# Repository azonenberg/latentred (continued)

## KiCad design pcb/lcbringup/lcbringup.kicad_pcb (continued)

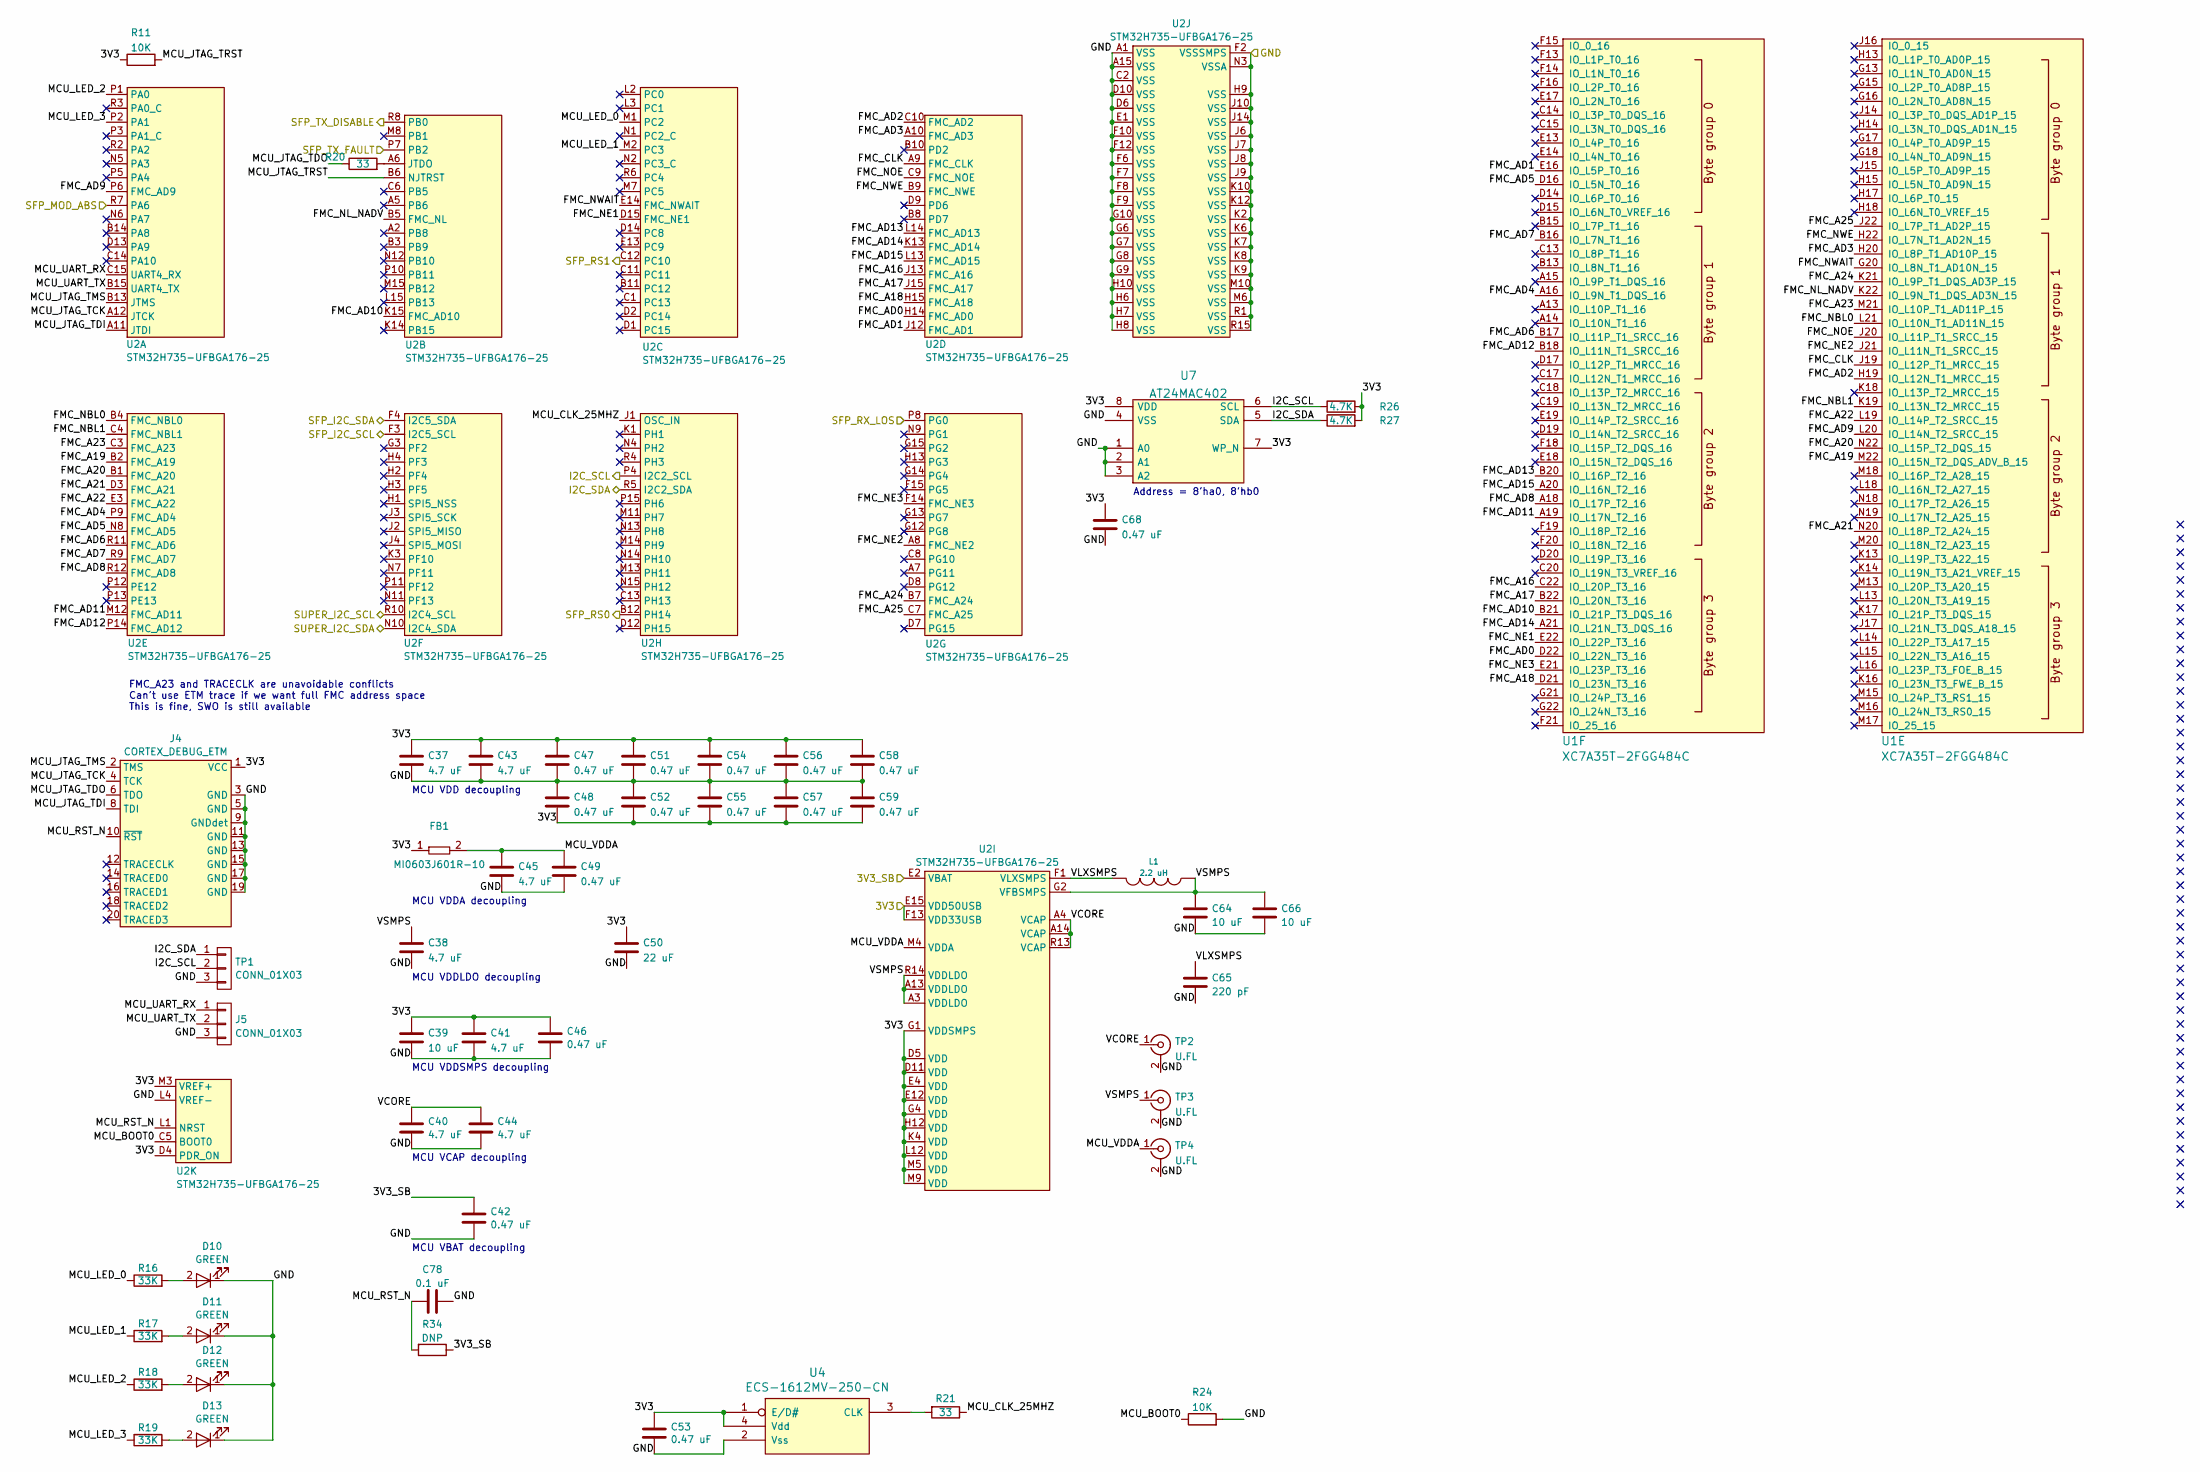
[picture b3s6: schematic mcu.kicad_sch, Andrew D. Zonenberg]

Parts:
C37, C38, C40, C41, C43, C44, C45: 4.7 uF; EIA_0603_CAP_NOSILK
C39, C64, C66: 10 uF; EIA_0805_CAP_NOSILK
C42, C46, C47, C48, C49, C51, C52, C53, C54, C55, C56, C57, C58, C59, C68: 0.47 uF; EIA_0402_CAP_NOSILK
C50: 22 uF; EIA_0805_CAP_NOSILK
C65: 220 pF; EIA_0402_CAP_NOSILK
C78: 0.1 uF; EIA_0402_CAP_NOSILK
D10, D11, D12, D13: GREEN; EIA_0402_LED
FB1: MI0603J601R-10; EIA_0603_INDUCTOR_NOSILK
J4: CORTEX_DEBUG_ETM; CONN_HEADER_1.27MM_2x10_SMT_SAMTEC_FTSH-110-01-L-DV-K
J5: CONN_01X03; CONN_HEADER_2.54MM_1x3_REFLOW
L1: 2.2 uH; EIA_1210_CAP_NOSILK
R11, R24: 10K; EIA_0402_RES_NOSILK
R16, R17, R18, R19: 33K; EIA_0402_RES_NOSILK
R20, R21: 33; EIA_0402_RES_NOSILK
R26, R27: 4.7K; EIA_0402_RES_NOSILK
R34: DNP; EIA_0402_RES_NOSILK
TP1: CONN_01X03; CONN_HEADER_2.54MM_1x3_REFLOW
TP2, TP3, TP4: U.FL; CONN_U.FL_TE_1909763-1
U1: XC7A35T-2FGG484C; BGA_484_22x22_FULLARRAY_1MM
U2: STM32H735-UFBGA176-25; BGA_201_10x10_DEPOP_0.65MM_OSHPARK
U4: ECS-1612MV-250-CN; OSCILLATOR_1.6x1.2
U7: AT24MAC402; DFN_8_0.5MM_2x3MM_TALL

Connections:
/3V3: C37.1, C39.1, C41.1, C43.1, C46.1, C47.1, C48.2, C50.1, C51.1, C52.2, C53.1, C54.1, C55.2, C56.1, C57.2, C58.1, C59.2, C68.1, FB1.1, J4.1 (VCC), R11.1, R26.2, R27.2, U2.D4 (PDR_ON), U2.D5 (VDD), U2.D11 (VDD), U2.E4 (VDD), U2.E12 (VDD), U2.E15 (VDD50USB), U2.F13 (VDD33USB), U2.G1 (VDDSMPS), U2.G4 (VDD), U2.H12 (VDD), U2.K4 (VDD), U2.L12 (VDD), U2.M3 (VREF+), U2.M5 (VDD), U2.M9 (VDD), U4.1 (E/D#), U4.4 (Vdd), U7.7 (WP_N), U7.8 (VDD); also elsewhere on the board
/3V3_SB: C42.1, R34.1, U2.E2 (VBAT); also elsewhere on the board
/GND: C37.2, C38.2, C39.2, C40.2, C41.2, C42.2, C43.2, C44.2, C45.2, C46.2, C47.2, C48.1, C49.2, C50.2, C51.2, C52.1, C53.2, C54.2, C55.1, C56.2, C57.1, C58.2, C59.1, C64.2, C65.2, C66.2, C68.2, C78.2, D10.1 (K), D11.1 (K), D12.1 (K), D13.1 (K), J4.3 (GND), J4.5 (GND), J4.9 (GNDdet), J4.11 (GND), J4.13 (GND), J4.15 (GND), J4.17 (GND), J4.19 (GND), J5.3, R24.2, TP1.3, TP2.2 (Ext), TP3.2 (Ext), TP4.2 (Ext), U2.A1 (VSS), U2.A15 (VSS), U2.C2 (VSS), U2.D6 (VSS), U2.D10 (VSS), U2.E1 (VSS), U2.F2 (VSSSMPS), U2.F6 (VSS), U2.F7 (VSS), U2.F8 (VSS), U2.F9 (VSS), U2.F10 (VSS), U2.F12 (VSS), U2.G6 (VSS), U2.G7 (VSS), U2.G8 (VSS), U2.G9 (VSS), U2.G10 (VSS), U2.H6 (VSS), U2.H7 (VSS), U2.H8 (VSS), U2.H9 (VSS), U2.H10 (VSS), U2.J6 (VSS), U2.J7 (VSS), U2.J8 (VSS), U2.J9 (VSS), U2.J10 (VSS), U2.J14 (VSS), U2.K2 (VSS), U2.K6 (VSS), U2.K7 (VSS), U2.K8 (VSS), U2.K9 (VSS), U2.K10 (VSS), U2.K12 (VSS), U2.L4 (VREF-), U2.M6 (VSS), U2.M10 (VSS), U2.N3 (VSSA), U2.R1 (VSS), U2.R15 (VSS), U4.2 (Vss), U7.1 (A0), U7.2 (A1), U7.3 (A2), U7.4 (VSS); also elsewhere on the board
/MCU/FMC_A16: U1.C22 (IO_L20P_T3_16), U2.J13 (FMC_A16)
/MCU/FMC_A17: U1.B22 (IO_L20N_T3_16), U2.J15 (FMC_A17)
/MCU/FMC_A18: U1.D21 (IO_L23N_T3_16), U2.H15 (FMC_A18)
/MCU/FMC_A19: U1.M22 (IO_L15N_T2_DQS_ADV_B_15), U2.B2 (FMC_A19)
/MCU/FMC_A20: U1.N22 (IO_L15P_T2_DQS_15), U2.B1 (FMC_A20)
/MCU/FMC_A21: U1.N20 (IO_L18P_T2_A24_15), U2.D3 (FMC_A21)
/MCU/FMC_A22: U1.L19 (IO_L14P_T2_SRCC_15), U2.E3 (FMC_A22)
/MCU/FMC_A23: U1.M21 (IO_L10P_T1_AD11P_15), U2.C3 (FMC_A23)
/MCU/FMC_A24: U1.K21 (IO_L9P_T1_DQS_AD3P_15), U2.B7 (FMC_A24)
/MCU/FMC_A25: U1.J22 (IO_L7P_T1_AD2P_15), U2.C7 (FMC_A25)
/MCU/FMC_AD0: U1.D22 (IO_L22N_T3_16), U2.H14 (FMC_AD0)
/MCU/FMC_AD1: U1.E16 (IO_L5P_T0_16), U2.J12 (FMC_AD1)
/MCU/FMC_AD2: U1.H19 (IO_L12N_T1_MRCC_15), U2.C10 (FMC_AD2)
/MCU/FMC_AD3: U1.H20 (IO_L8P_T1_AD10P_15), U2.A10 (FMC_AD3)
/MCU/FMC_AD4: U1.A16 (IO_L9N_T1_DQS_16), U2.P9 (FMC_AD4)
/MCU/FMC_AD5: U1.D16 (IO_L5N_T0_16), U2.N8 (FMC_AD5)
/MCU/FMC_AD6: U1.B17 (IO_L11P_T1_SRCC_16), U2.R11 (FMC_AD6)
/MCU/FMC_AD7: U1.B16 (IO_L7N_T1_16), U2.R9 (FMC_AD7)
/MCU/FMC_AD8: U1.A18 (IO_L17P_T2_16), U2.R12 (FMC_AD8)
/MCU/FMC_AD9: U1.L20 (IO_L14N_T2_SRCC_15), U2.P6 (FMC_AD9)
/MCU/FMC_AD10: U1.B21 (IO_L21P_T3_DQS_16), U2.K15 (FMC_AD10)
/MCU/FMC_AD11: U1.A19 (IO_L17N_T2_16), U2.M12 (FMC_AD11)
/MCU/FMC_AD12: U1.B18 (IO_L11N_T1_SRCC_16), U2.P14 (FMC_AD12)
/MCU/FMC_AD13: U1.B20 (IO_L16P_T2_16), U2.L14 (FMC_AD13)
/MCU/FMC_AD14: U1.A21 (IO_L21N_T3_DQS_16), U2.K13 (FMC_AD14)
/MCU/FMC_AD15: U1.A20 (IO_L16N_T2_16), U2.L13 (FMC_AD15)
/MCU/FMC_CLK: U1.J19 (IO_L12P_T1_MRCC_15), U2.A9 (FMC_CLK)
/MCU/FMC_NBL0: U1.L21 (IO_L10N_T1_AD11N_15), U2.B4 (FMC_NBL0)
/MCU/FMC_NBL1: U1.K19 (IO_L13N_T2_MRCC_15), U2.C4 (FMC_NBL1)
/MCU/FMC_NE1: U1.E22 (IO_L22P_T3_16), U2.D15 (FMC_NE1)
/MCU/FMC_NE2: U1.J21 (IO_L11N_T1_SRCC_15), U2.A8 (FMC_NE2)
/MCU/FMC_NE3: U1.E21 (IO_L23P_T3_16), U2.F14 (FMC_NE3)
/MCU/FMC_NL_NADV: U1.K22 (IO_L9N_T1_DQS_AD3N_15), U2.B5 (FMC_NL)
/MCU/FMC_NOE: U1.J20 (IO_L11P_T1_SRCC_15), U2.C9 (FMC_NOE)
/MCU/FMC_NWAIT: U1.G20 (IO_L8N_T1_AD10N_15), U2.E14 (FMC_NWAIT)
/MCU/FMC_NWE: U1.H22 (IO_L7N_T1_AD2N_15), U2.B9 (FMC_NWE)
/MCU/I2C_SCL: R26.1, TP1.2, U2.P4 (I2C2_SCL), U7.6 (SCL); also elsewhere on the board
/MCU/I2C_SDA: R27.1, TP1.1, U2.R5 (I2C2_SDA), U7.5 (SDA); also elsewhere on the board
/MCU/MCU_BOOT0: R24.1, U2.C5 (BOOT0)
/MCU/MCU_CLK_25MHZ: R21.1, U2.J1 (OSC_IN)
/MCU/MCU_JTAG_TCK: J4.4 (TCK), U2.A12 (JTCK)
/MCU/MCU_JTAG_TDI: J4.8 (TDI), U2.A11 (JTDI)
/MCU/MCU_JTAG_TDO: J4.6 (TDO), R20.1
/MCU/MCU_JTAG_TMS: J4.2 (TMS), U2.B13 (JTMS)
/MCU/MCU_JTAG_TRST: R11.2, U2.B6 (NJTRST)
/MCU/MCU_LED_0: R16.1, U2.M1 (PC2)
/MCU/MCU_LED_1: R17.1, U2.M2 (PC3)
/MCU/MCU_LED_2: R18.1, U2.P1 (PA0)
/MCU/MCU_LED_3: R19.1, U2.P2 (PA1)
/MCU/MCU_RST_N: C78.1, J4.10 (~RST), R34.2, U2.L1 (NRST)
/MCU/MCU_UART_RX: J5.1, U2.C15 (UART4_RX)
/MCU/MCU_UART_TX: J5.2, U2.B15 (UART4_TX)
/MCU/MCU_VDDA: C45.1, C49.1, FB1.2, TP4.1 (In), U2.M4 (VDDA)
/MCU/SFP_MOD_ABS: U2.R7 (PA6); also elsewhere on the board
/MCU/SFP_RS0: U2.B12 (PH14); also elsewhere on the board
/MCU/SFP_RS1: U2.C12 (PC10); also elsewhere on the board
/MCU/SFP_RX_LOS: U2.P8 (PG0); also elsewhere on the board
/MCU/SFP_TX_DISABLE: U2.R8 (PB0); also elsewhere on the board
/MCU/SFP_TX_FAULT: U2.P7 (PB2); also elsewhere on the board
/MCU/VCORE: C40.1, C44.1, TP2.1 (In), U2.A4 (VCAP), U2.A14 (VCAP), U2.R13 (VCAP)
/MCU/VLXSMPS: C65.1, L1.2, U2.F1 (VLXSMPS)
/MCU/VSMPS: C38.1, C64.1, C66.1, L1.1, TP3.1 (In), U2.A3 (VDDLDO), U2.A13 (VDDLDO), U2.G2 (VFBSMPS), U2.R14 (VDDLDO)
/Power supply/SUPER_I2C_SCL: U2.R10 (I2C4_SCL); also elsewhere on the board
/Power supply/SUPER_I2C_SDA: U2.N10 (I2C4_SDA); also elsewhere on the board
/SFP/SFP_I2C_SCL: U2.F3 (I2C5_SCL); also elsewhere on the board
/SFP/SFP_I2C_SDA: U2.F4 (I2C5_SDA); also elsewhere on the board
unnamed: D10.2 (A), R16.2
unnamed: D11.2 (A), R17.2
unnamed: D12.2 (A), R18.2
unnamed: D13.2 (A), R19.2
unnamed: R20.2, U2.A6 (JTDO)
unnamed: R21.2, U4.3 (CLK)

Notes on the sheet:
MCU VDDA decoupling
Address = 8'ha0, 8'hb0
MCU VDDLDO decoupling
MCU VDDSMPS decoupling
MCU VBAT decoupling
MCU VDD decoupling
MCU VCAP decoupling
FMC_A23 and TRACECLK are unavoidable conflicts Can't use ETM trace if we want full FMC address space This is fine, SWO is still available

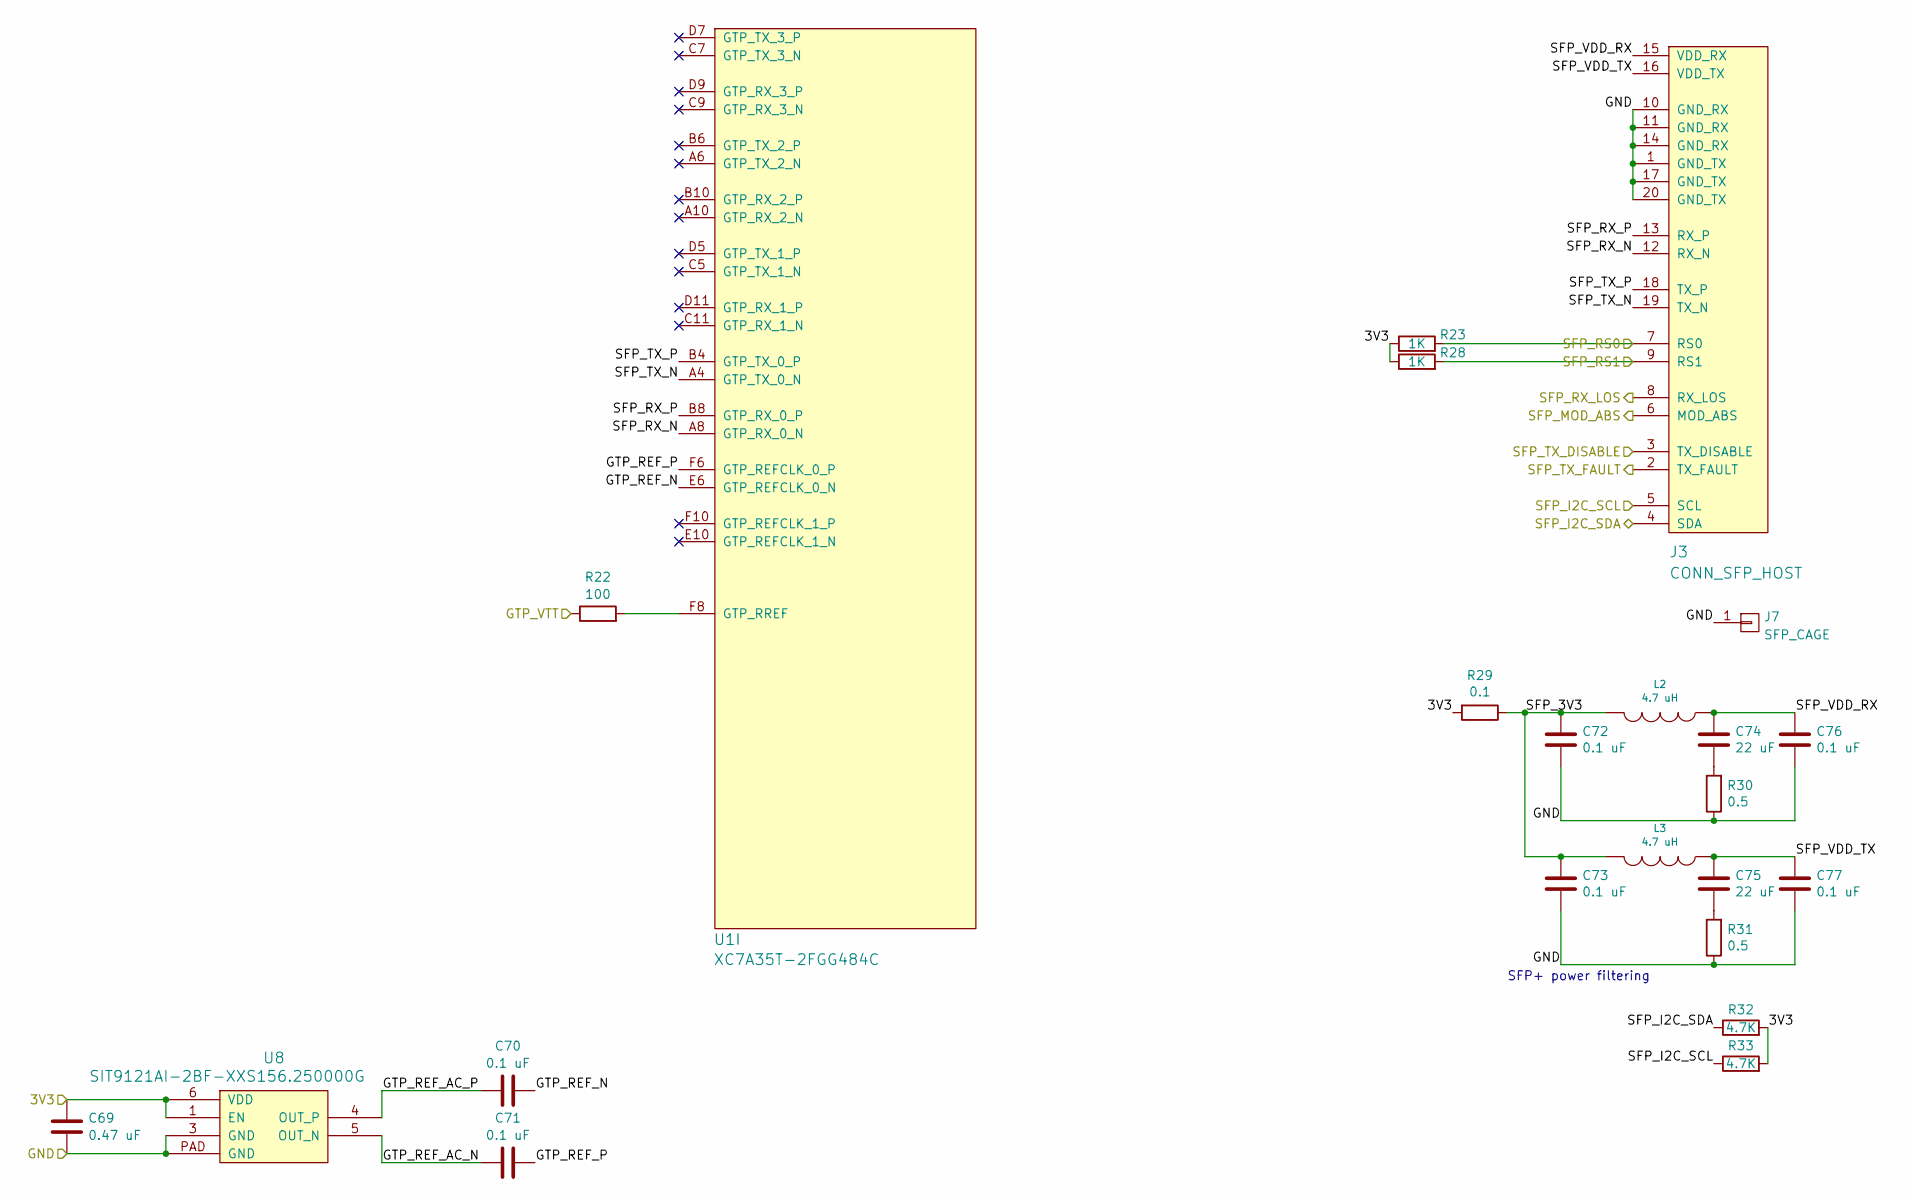
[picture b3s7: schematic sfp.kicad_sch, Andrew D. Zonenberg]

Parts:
C69: 0.47 uF; EIA_0402_CAP_NOSILK
C70, C71, C72, C73, C76, C77: 0.1 uF; EIA_0402_CAP_NOSILK
C74, C75: 22 uF; EIA_0805_CAP_NOSILK
J3: CONN_SFP_HOST; CONN_SFP+_AMPHENOL_UE76_A10_2000T
J7: SFP_CAGE; CONN_SFP_CAGE_TE_2007194-1
L2, L3: 4.7 uH; EIA_0805_INDUCTOR_NOSILK
R22: 100; EIA_0402_RES_NOSILK
R23, R28: 1K; EIA_0402_RES_NOSILK
R29: 0.1; EIA_0402_RES_NOSILK
R30, R31: 0.5; EIA_0402_RES_NOSILK
R32, R33: 4.7K; EIA_0402_RES_NOSILK
U1: XC7A35T-2FGG484C; BGA_484_22x22_FULLARRAY_1MM
U8: SIT9121AI-2BF-XXS156.250000G; OSCILLATOR_LVDS_3.2x2.5

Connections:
/1V2: R22.1; also elsewhere on the board
/3V3: C69.1, R23.1, R28.1, R29.2, R32.2, R33.2, U8.1 (EN), U8.6 (VDD); also elsewhere on the board
/GND: C69.2, C72.2, C73.2, C76.2, C77.2, J3.1 (GND_TX), J3.10 (GND_RX), J3.11 (GND_RX), J3.14 (GND_RX), J3.17 (GND_TX), J3.20 (GND_TX), J7.1, R30.1, R31.1, U8.3 (GND), U8.PAD (GND); also elsewhere on the board
/MCU/SFP_MOD_ABS: J3.6 (MOD_ABS); also elsewhere on the board
/MCU/SFP_RS0: J3.7 (RS0), R23.2; also elsewhere on the board
/MCU/SFP_RS1: J3.9 (RS1), R28.2; also elsewhere on the board
/MCU/SFP_RX_LOS: J3.8 (RX_LOS); also elsewhere on the board
/MCU/SFP_TX_DISABLE: J3.3 (TX_DISABLE); also elsewhere on the board
/MCU/SFP_TX_FAULT: J3.2 (TX_FAULT); also elsewhere on the board
/SFP/GTP_REF_AC_N: C71.1, U8.5 (OUT_N)
/SFP/GTP_REF_AC_P: C70.1, U8.4 (OUT_P)
/SFP/GTP_REF_N: C70.2, U1.E6 (GTP_REFCLK_0_N)
/SFP/GTP_REF_P: C71.2, U1.F6 (GTP_REFCLK_0_P)
/SFP/SFP_3V3: C72.1, C73.1, L2.2, L3.2, R29.1
/SFP/SFP_I2C_SCL: J3.5 (SCL), R33.1; also elsewhere on the board
/SFP/SFP_I2C_SDA: J3.4 (SDA), R32.1; also elsewhere on the board
/SFP/SFP_RX_N: J3.12 (RX_N), U1.A8 (GTP_RX_0_N)
/SFP/SFP_RX_P: J3.13 (RX_P), U1.B8 (GTP_RX_0_P)
/SFP/SFP_TX_N: J3.19 (TX_N), U1.A4 (GTP_TX_0_N)
/SFP/SFP_TX_P: J3.18 (TX_P), U1.B4 (GTP_TX_0_P)
/SFP/SFP_VDD_RX: C74.1, C76.1, J3.15 (VDD_RX), L2.1
/SFP/SFP_VDD_TX: C75.1, C77.1, J3.16 (VDD_TX), L3.1
unnamed: C74.2, R30.2
unnamed: C75.2, R31.2
unnamed: R22.2, U1.F8 (GTP_RREF)

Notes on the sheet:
SFP+ power filtering

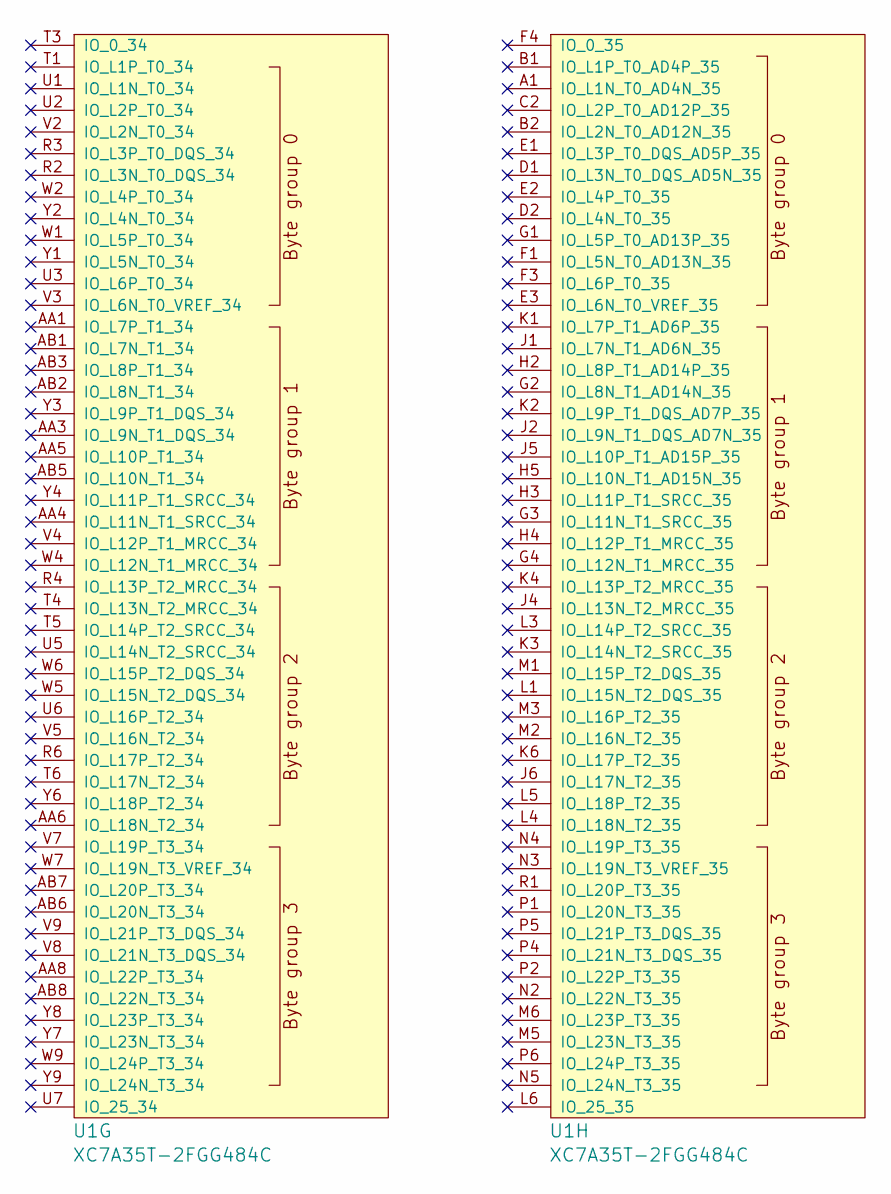
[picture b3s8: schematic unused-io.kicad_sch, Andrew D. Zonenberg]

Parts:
U1: XC7A35T-2FGG484C; BGA_484_22x22_FULLARRAY_1MM

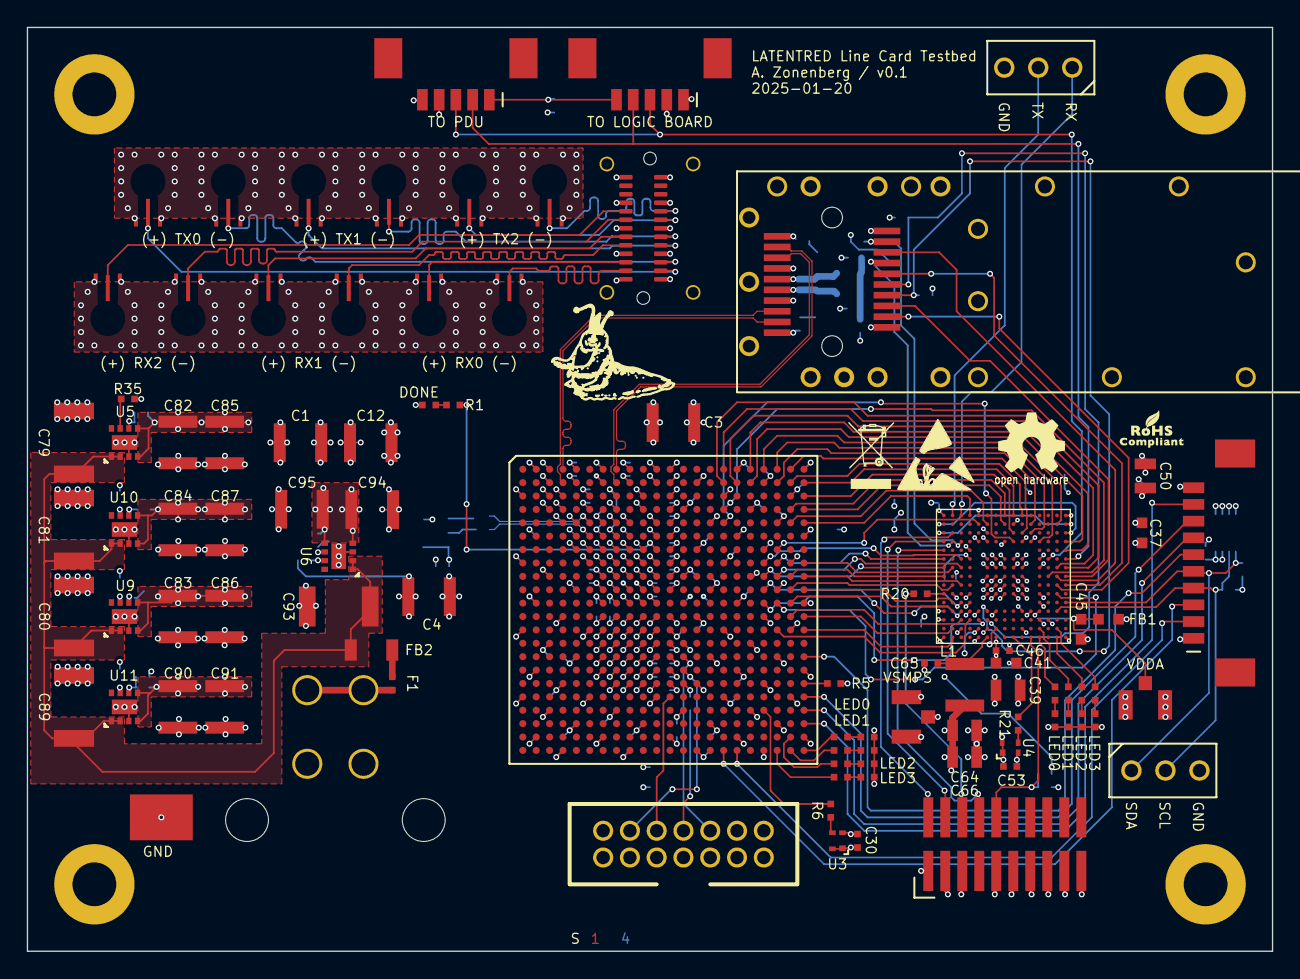
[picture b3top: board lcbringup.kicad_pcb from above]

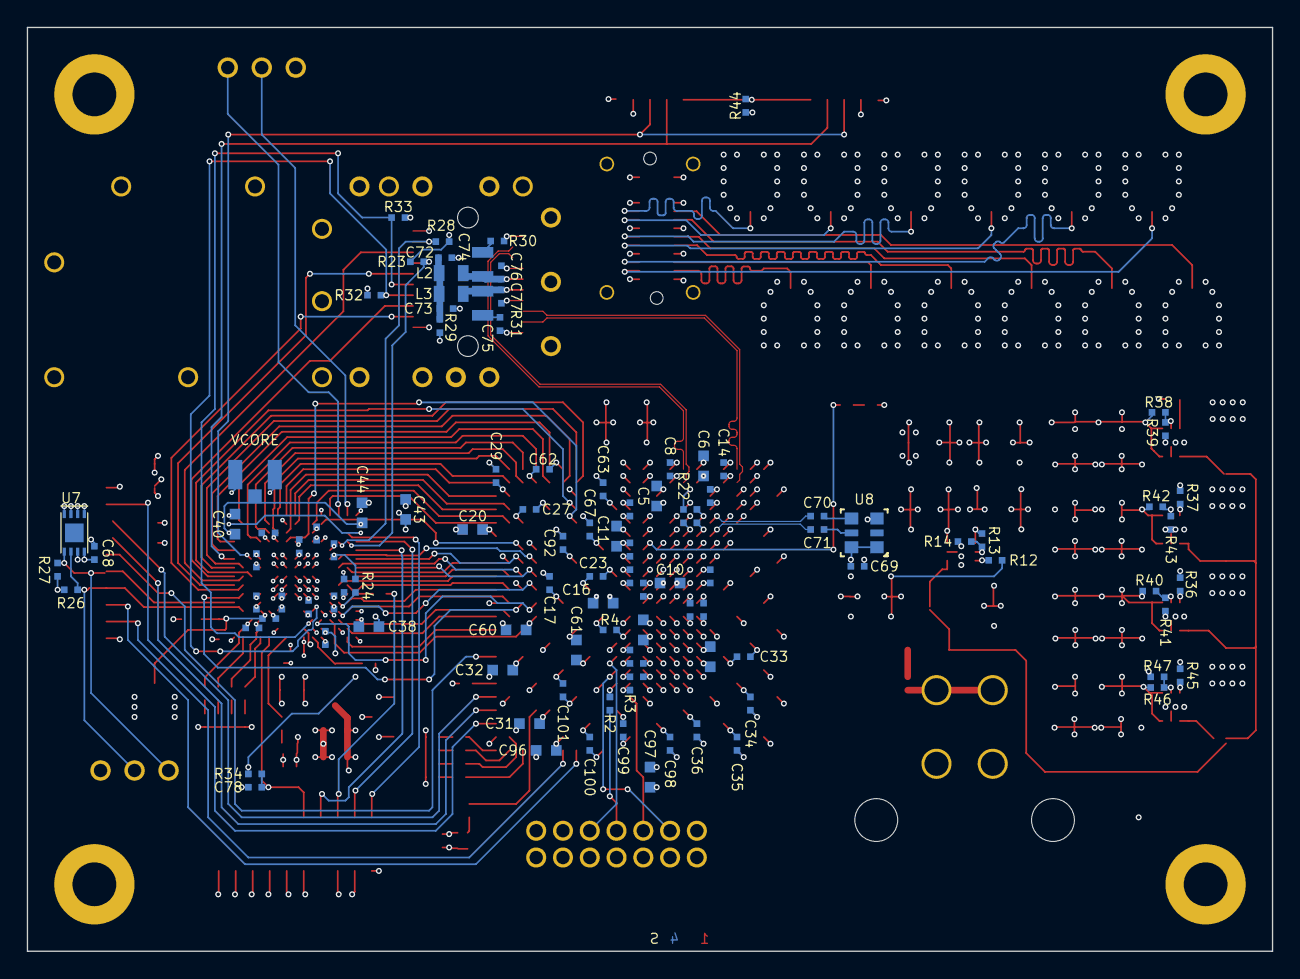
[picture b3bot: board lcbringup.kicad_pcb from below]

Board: 4 copper layers, 93.0 x 69.0 mm, 207 parts (106 on the bottom side), 145 nets.

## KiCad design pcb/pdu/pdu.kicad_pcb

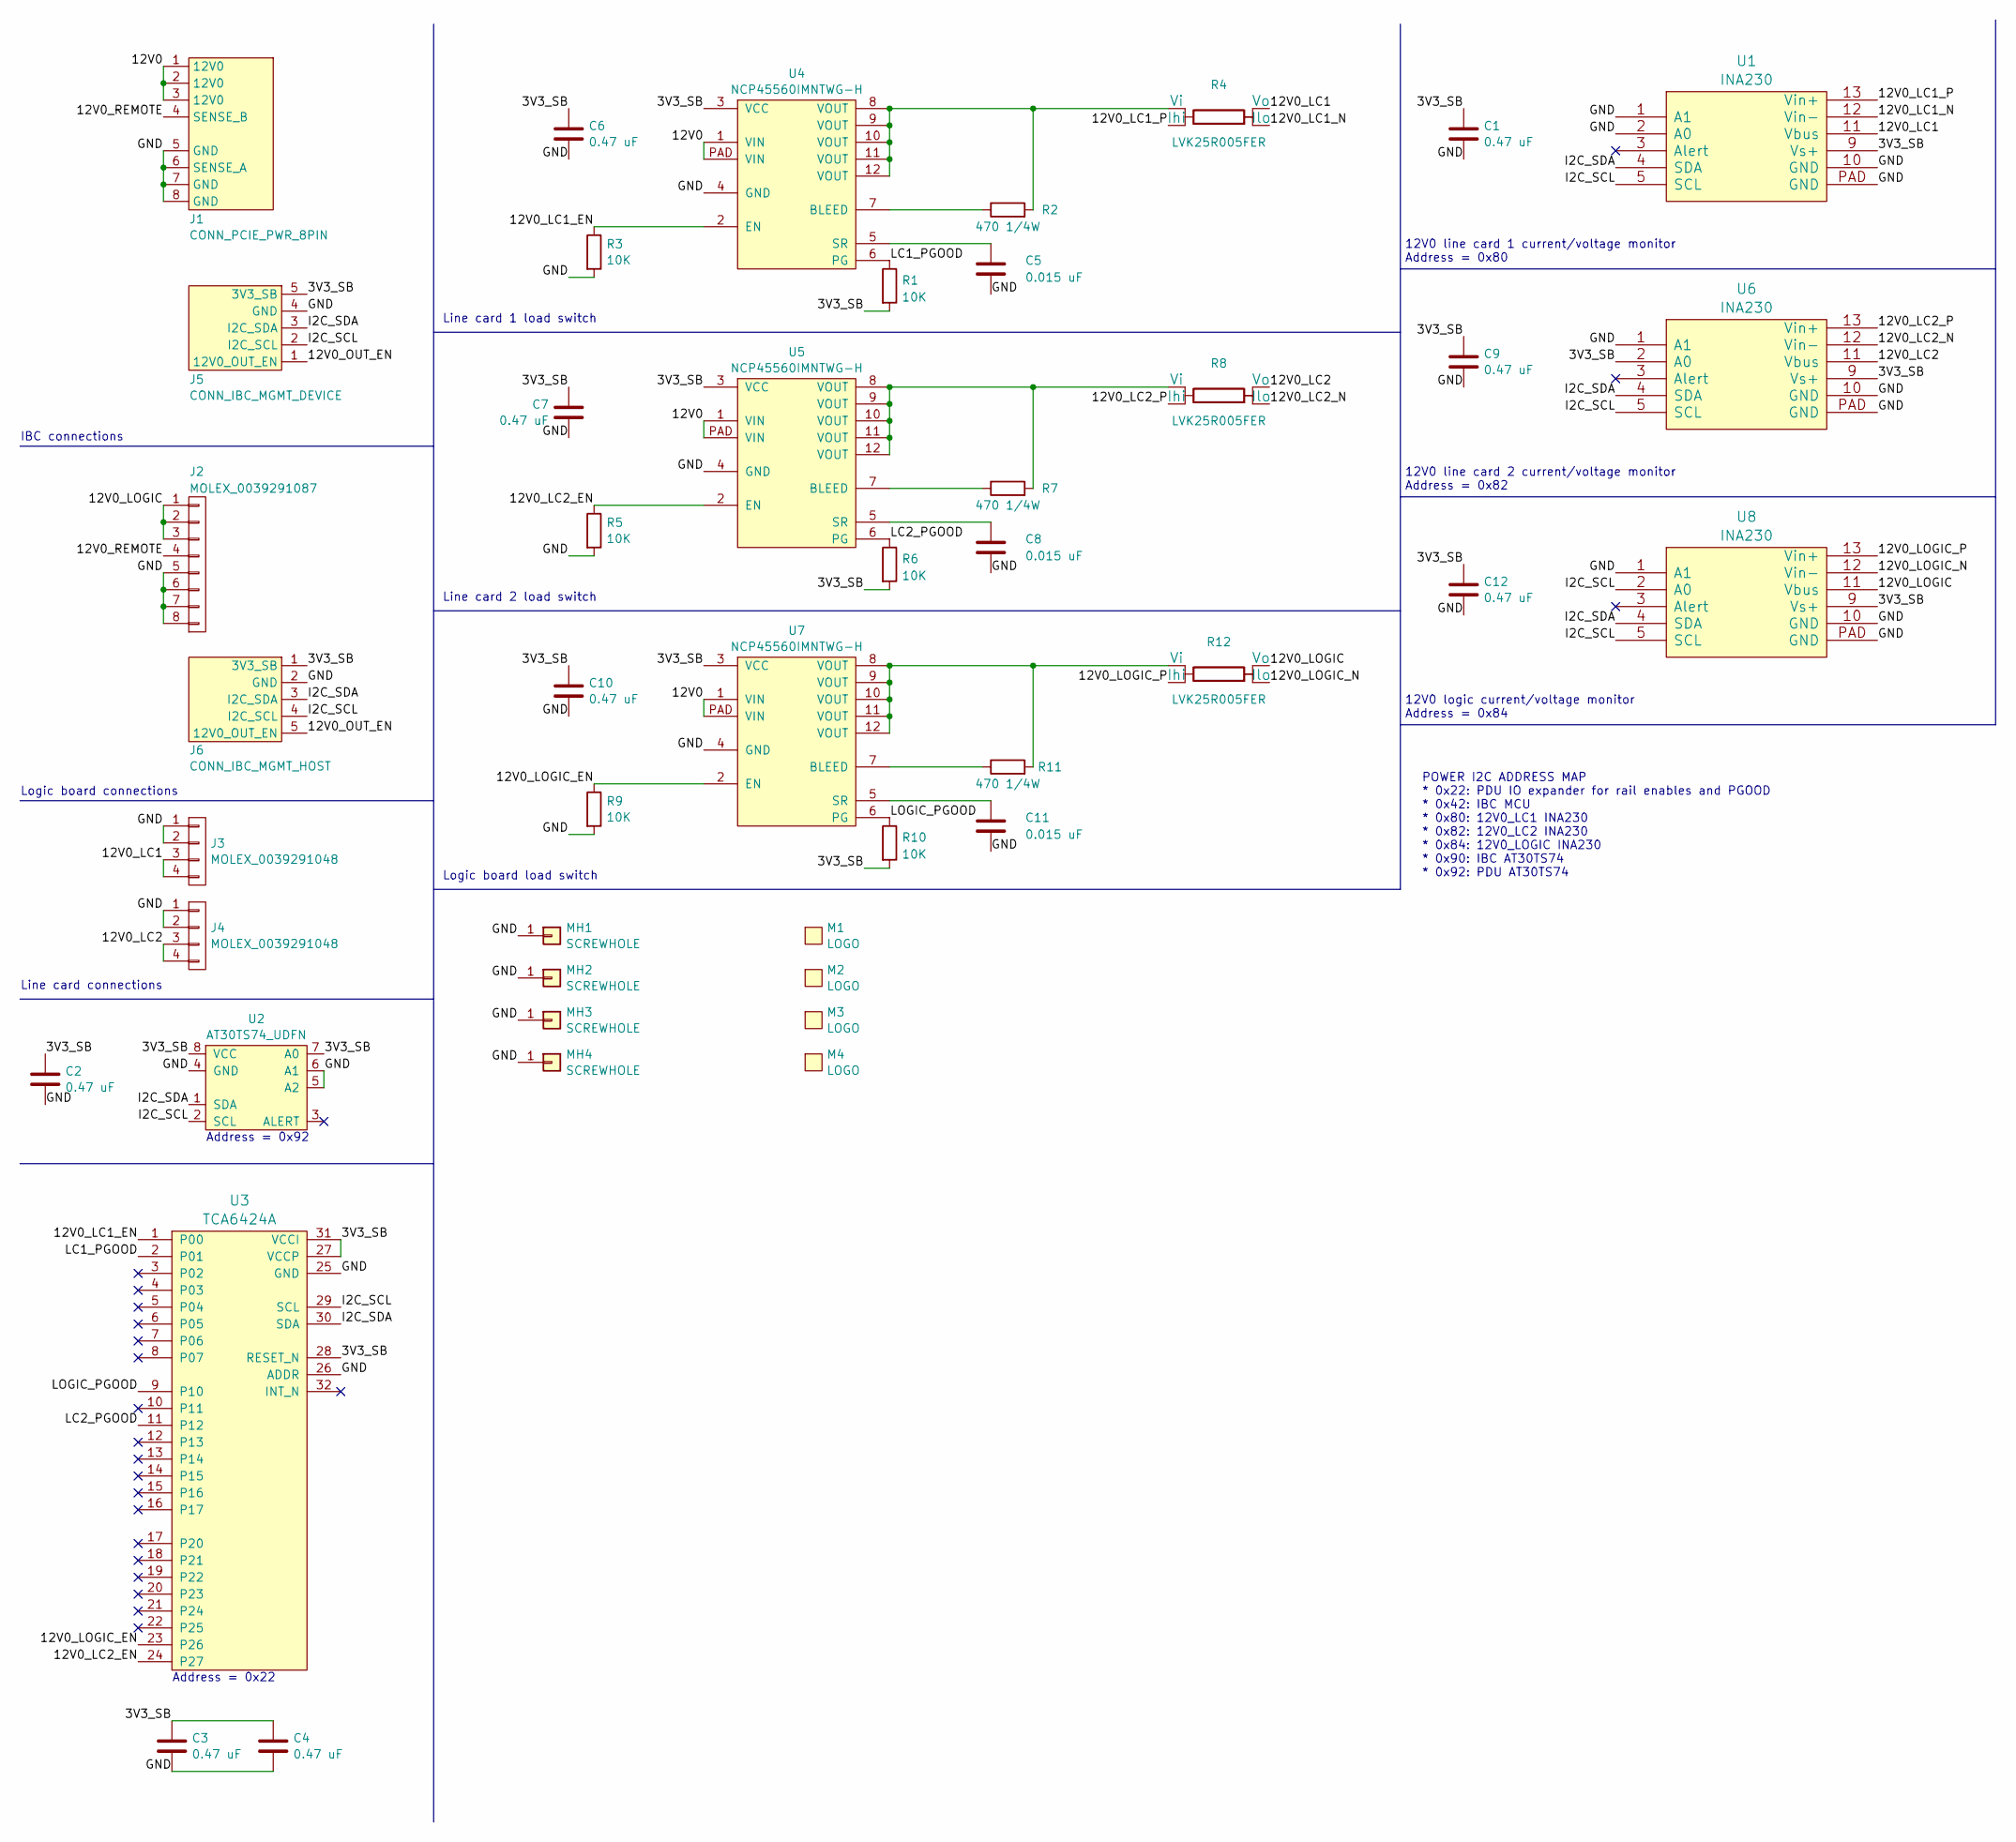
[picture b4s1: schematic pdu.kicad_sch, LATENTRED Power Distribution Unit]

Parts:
C1, C2, C3, C4, C6, C7, C9, C10, C12: 0.47 uF; EIA_0402_CAP_NOSILK
C5, C8, C11: 0.015 uF; EIA_0603_CAP_NOSILK
J1: CONN_PCIE_PWR_8PIN; CONN_MOLEX_MINIFITJR_8POS_0039291087
J2: MOLEX_0039291087; CONN_MOLEX_MINIFITJR_8POS_0039291087
J3, J4: MOLEX_0039291048; CONN_MOLEX_MINIFITJR_4POS_0039291048
J5: CONN_IBC_MGMT_DEVICE; CONN_MOLEX_PICOBLADE_5POS_0532610571
J6: CONN_IBC_MGMT_HOST; CONN_MOLEX_PICOBLADE_5POS_0532610571
M1: LOGO; LONGTHING-1200DPI
M2: LOGO; Logo_silk_WEEE_3.4x5mm
M3: LOGO; Logo_silk_ROHS_5x2.8mm
M4: LOGO; Logo_silk_OSHW_6x6mm
MH1, MH2, MH3, MH4: SCREWHOLE; MECHANICAL_CLEARANCEHOLE_4_40
R1, R3, R5, R6, R9, R10: 10K; EIA_0402_RES_NOSILK
R2, R7, R11: 470 1/4W; EIA_0603_RES_NOSILK
R4, R8, R12: LVK25R005FER; OHMITE_LVK25
U1, U6, U8: INA230; QFN_16_0.5MM_3x3MM
U2: AT30TS74_UDFN; DFN_8_0.5MM_2x3MM_TALL
U3: TCA6424A; QFN_32_0.5MM_5x5MM
U4, U5, U7: NCP45560IMNTWG-H; DFN_12_0.5MM_3x3MM

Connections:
/3V3_SB: C1.1, C2.1, C3.1, C4.1, C6.1, C7.1, C9.1, C10.1, C12.1, J5.5 (3V3_SB), J6.1 (3V3_SB), R1.2, R6.2, R10.2, U1.9 (Vs+), U2.7 (A0), U2.8 (VCC), U3.27 (VCCP), U3.28 (RESET_N), U3.31 (VCCI), U4.3 (VCC), U5.3 (VCC), U6.2 (A0), U6.9 (Vs+), U7.3 (VCC), U8.9 (Vs+)
/12V0: J1.1 (12V0), J1.2 (12V0), J1.3 (12V0), U4.1 (VIN), U4.PAD (VIN), U5.1 (VIN), U5.PAD (VIN), U7.1 (VIN), U7.PAD (VIN)
/12V0_LC1: J3.3, J3.4, R4.2 (Vo), U1.11 (Vbus)
/12V0_LC1_EN: R3.1, U3.1 (P00), U4.2 (EN)
/12V0_LC1_N: R4.1 (Ilo), U1.12 (Vin-)
/12V0_LC1_P: R4.3 (Ihi), U1.13 (Vin+)
/12V0_LC2: J4.3, J4.4, R8.2 (Vo), U6.11 (Vbus)
/12V0_LC2_EN: R5.1, U3.24 (P27), U5.2 (EN)
/12V0_LC2_N: R8.1 (Ilo), U6.12 (Vin-)
/12V0_LC2_P: R8.3 (Ihi), U6.13 (Vin+)
/12V0_LOGIC: J2.1, J2.2, J2.3, R12.2 (Vo), U8.11 (Vbus)
/12V0_LOGIC_EN: R9.1, U3.23 (P26), U7.2 (EN)
/12V0_LOGIC_N: R12.1 (Ilo), U8.12 (Vin-)
/12V0_LOGIC_P: R12.3 (Ihi), U8.13 (Vin+)
/12V0_OUT_EN: J5.1 (12V0_OUT_EN), J6.5 (12V0_OUT_EN)
/12V0_REMOTE: J1.4 (SENSE_B), J2.4
/GND: C1.2, C2.2, C3.2, C4.2, C5.2, C6.2, C7.2, C8.2, C9.2, C10.2, C11.2, C12.2, J1.5 (GND), J1.6 (SENSE_A), J1.7 (GND), J1.8 (GND), J2.5, J2.6, J2.7, J2.8, J3.1, J3.2, J4.1, J4.2, J5.4 (GND), J6.2 (GND), MH1.1, MH2.1, MH3.1, MH4.1, R3.2, R5.2, R9.2, U1.1 (A1), U1.2 (A0), U1.10 (GND), U1.PAD (GND), U2.4 (GND), U2.5 (A2), U2.6 (A1), U3.25 (GND), U3.26 (ADDR), U4.4 (GND), U5.4 (GND), U6.1 (A1), U6.10 (GND), U6.PAD (GND), U7.4 (GND), U8.1 (A1), U8.10 (GND), U8.PAD (GND)
/I2C_SCL: J5.2 (I2C_SCL), J6.4 (I2C_SCL), U1.5 (SCL), U2.2 (SCL), U3.29 (SCL), U6.5 (SCL), U8.2 (A0), U8.5 (SCL)
/I2C_SDA: J5.3 (I2C_SDA), J6.3 (I2C_SDA), U1.4 (SDA), U2.1 (SDA), U3.30 (SDA), U6.4 (SDA), U8.4 (SDA)
/LC1_PGOOD: R1.1, U3.2 (P01), U4.6 (PG)
/LC2_PGOOD: R6.1, U3.11 (P12), U5.6 (PG)
/LOGIC_PGOOD: R10.1, U3.9 (P10), U7.6 (PG)
unnamed: R2.2, R4.4 (Vi), U4.8 (VOUT), U4.9 (VOUT), U4.10 (VOUT), U4.11 (VOUT), U4.12 (VOUT)
unnamed: R7.2, R8.4 (Vi), U5.8 (VOUT), U5.9 (VOUT), U5.10 (VOUT), U5.11 (VOUT), U5.12 (VOUT)
unnamed: R11.2, R12.4 (Vi), U7.8 (VOUT), U7.9 (VOUT), U7.10 (VOUT), U7.11 (VOUT), U7.12 (VOUT)
unnamed: R2.1, U4.7 (BLEED)
unnamed: C5.1, U4.5 (SR)
unnamed: R7.1, U5.7 (BLEED)
unnamed: C8.1, U5.5 (SR)
unnamed: R11.1, U7.7 (BLEED)
unnamed: C11.1, U7.5 (SR)

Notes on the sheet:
12V0 line card 1 current/voltage monitor Address = 0x80
Line card connections
12V0 line card 2 current/voltage monitor Address = 0x82
Address = 0x92
Line card 1 load switch
Address = 0x22
POWER I2C ADDRESS MAP * 0x22: PDU IO expander for rail enables and PGOOD * 0x42: IBC MCU * 0x80: 12V0_LC1 INA230 * 0x82: 12V0_LC2 INA230 * 0x84: 12V0_LOGIC INA230 * 0x90: IBC AT30TS74 * 0x92: PDU AT30TS74
Line card 2 load switch
IBC connections
12V0 logic current/voltage monitor Address = 0x84
Logic board load switch
Logic board connections

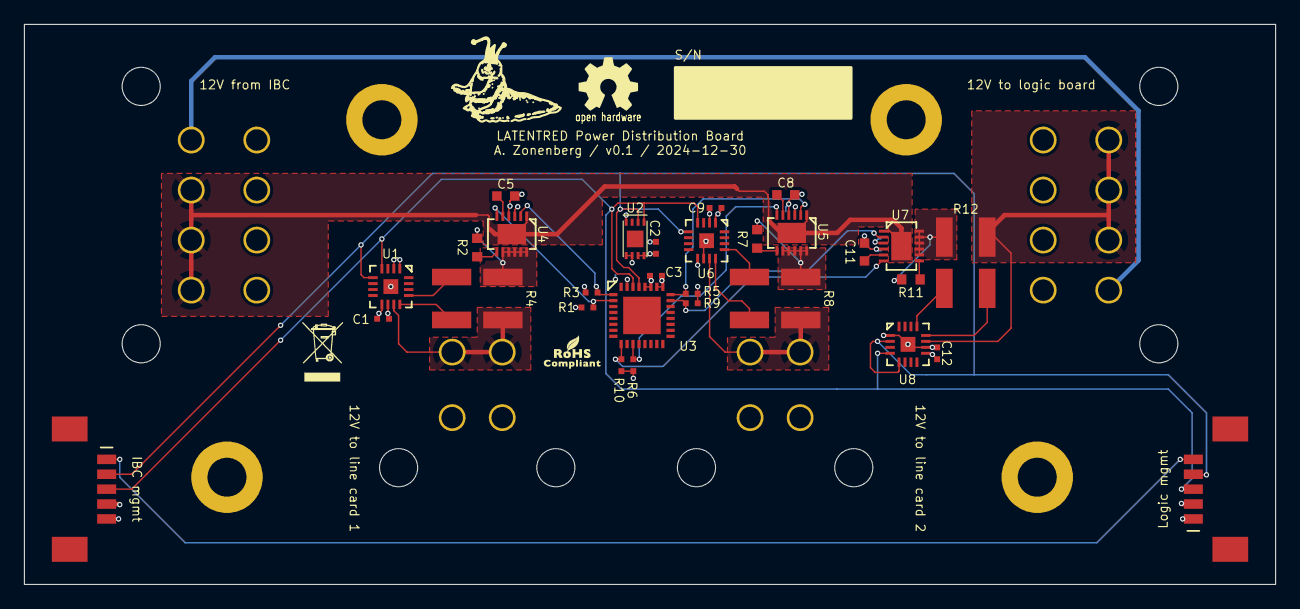
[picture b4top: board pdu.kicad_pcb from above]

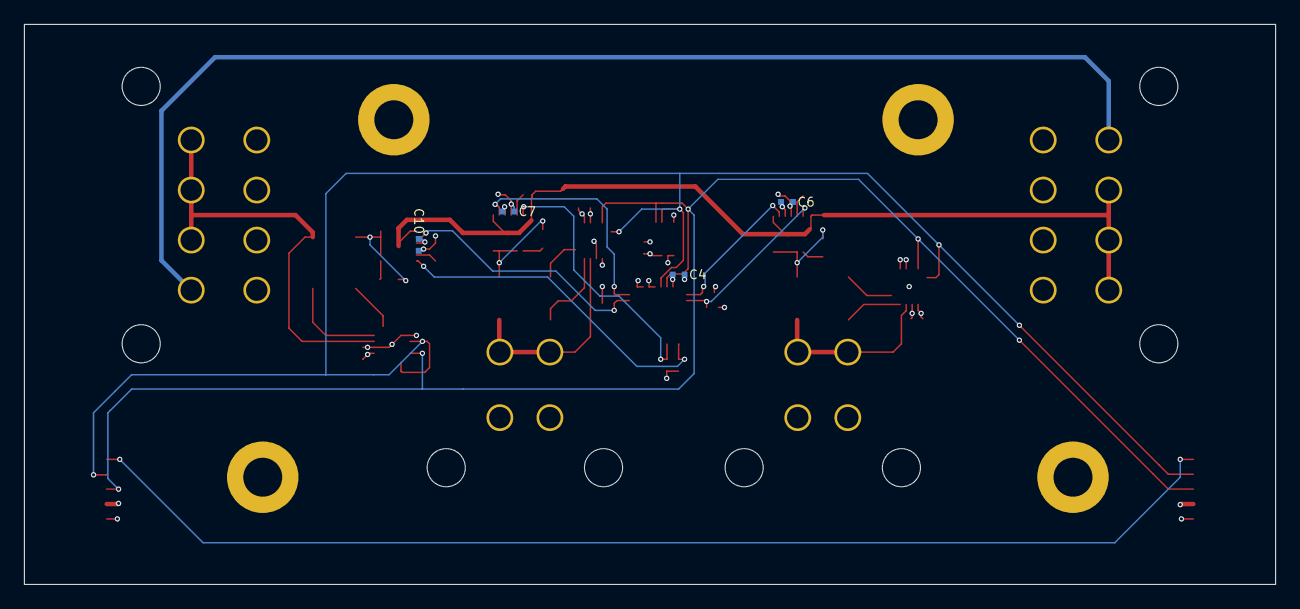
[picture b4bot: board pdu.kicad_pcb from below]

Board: 4 copper layers, 105.0 x 47.0 mm, 46 parts (4 on the bottom side), 31 nets.
